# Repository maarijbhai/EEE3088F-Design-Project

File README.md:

# Micro Mouse Power Subsystem

This respository contains the datasheets of components used, schematics and production files of a power subsystem of a Micro Mouse. The power subsystem handles the charging, battery monitoring, motor controll and providing power to the various other subsections of a Micro Mouse.

## Table of Contents
- [Overview](#overview)
- [Subsytem Requirements](#subsystem-requirements)
- [File Structure](file-structure)
- [Usage](#usage)
- [Production](#production)
- [Credits](credits)

## Overview

Designed to navigate and solve a maze by itself, the Micro Mouse is a common project with even competitions made to determine who is able to create the fastest and most efficient Micro Mouse. While not on the competition level this project is undertaken by students in the University of Cape Town to put into practice all the theoretical knowledge learnt in their studies. With the hardware and sensoring subsystem designed by the university, the aim of this project is to design the power subsystem that powers the overall design.

## Subsystem Requirements

- Operate up to 4 motors bidirectionally with the pins available to you (listed in the power pinout table). You will need to control 2x brushed DC motors which could each draw 200mA at the highest voltage of a 1S1P battery (the battery is further specified in the battery section). The other 2x motors are for the auxiliary connection and need to operate 500mA each.
- Place an INA219 for monitoring the battery on the I2C Bus and configure it correctly with respect to the hardware (cannot have BOTH A0 AND A1 on GND)
- Charge the battery from the 9V input pin (listed in the power pinout table).
- Have two charging modes for a higher and lower charging current for the battery (200mA, and approximately 600mA ±100mA from the battery perspective.
- Integrate USB C and get 9V out of the USB Host
- Provide 2x External Load Switching at 1A each (High Side connected to your 5V)
- Provide a 3V3 5% accuracy (300mA max) and 5V Out 5% accuracy (1.5A max)
- Provide an ON/OFF switch. OFF state: battery draw <30uA. ON state: can provide your robot peak current of 2A. The switch needs to shut down 5V and 3V3.

## File Structure

Each of the above mentioned requirements are designed seperately under their own folder name ultimately meeting up in the Main project folder. This was to prevent any clashes or errors arising from outdated revisions of the project being worked on. 

The production files (gerbers) can be found inside the Main project folder under "JLCPCB".

## Usage

# Access schematic or PCB:
To view or modify the schematic and/or PCB:
1. Open KiCad 9 or later
2. Load the Main project (or any other desired)
3. Edit or simulate as needed

# To manufacture the PCB:
1. Navigate to the JLCPCB website
2. Upload the Gerber ZIP file
3. Use the provided BOM and CPL files in the JLCPCB file directory inside the main project folder for assembly

## Credits
- Maarij Alam
- Saeed Solomon

Third-party components from Texas Instruments, ON Semiconductor, and others.

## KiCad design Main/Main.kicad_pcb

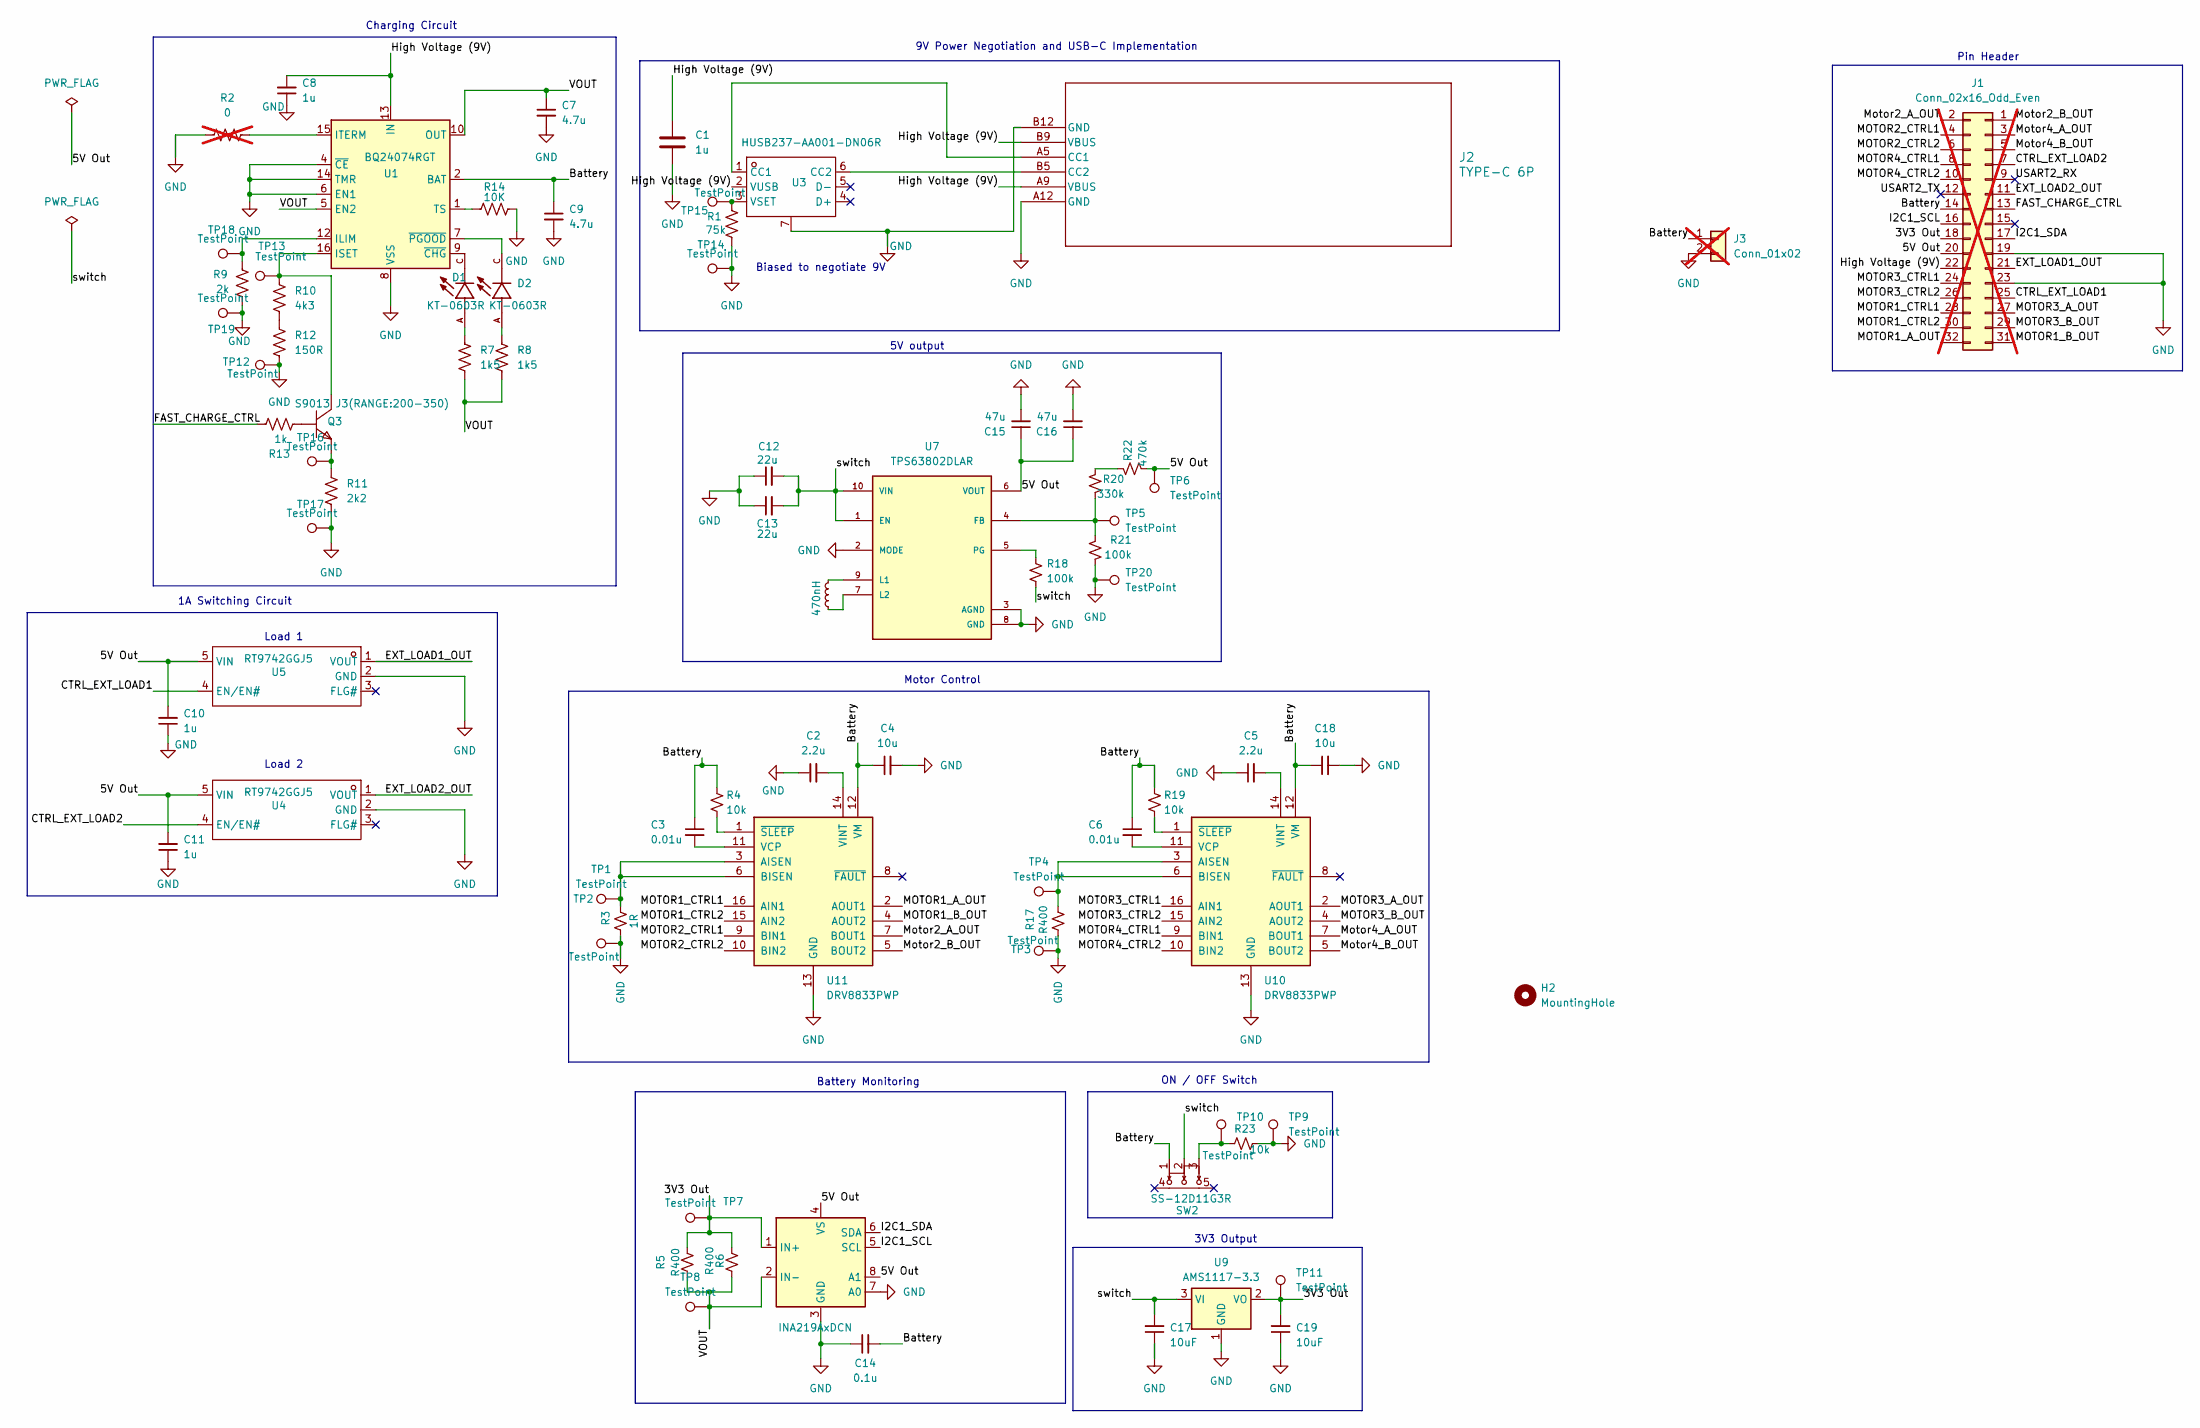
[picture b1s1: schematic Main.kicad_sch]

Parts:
C1, C8, C10, C11: 1u; C_1206_3216Metric_Pad1.33x1.80mm_HandSolder; LCSC C1848
C2, C5: 2.2u; C_0402_1005Metric_Pad0.74x0.62mm_HandSolder; LCSC C12530
C3, C6: 0.01u; C_0805_2012Metric_Pad1.18x1.45mm_HandSolder; LCSC C1710
C4, C18: 10u; C_0402_1005Metric_Pad0.74x0.62mm_HandSolder; LCSC C15525
C7: 4.7u; C_0402_1005Metric; LCSC C23733
C9: 4.7u; C_0402_1005Metric_Pad0.74x0.62mm_HandSolder; LCSC C23733
C12, C13: 22u; C_0402_1005Metric_Pad0.74x0.62mm_HandSolder; LCSC C45783
C14: 0.1u; C_0603_1608Metric_Pad1.08x0.95mm_HandSolder; LCSC C14663
C15, C16: 47u; C_0402_1005Metric_Pad0.74x0.62mm_HandSolder; LCSC C96123
C17, C19: 10uF; C_0402_1005Metric_Pad0.74x0.62mm_HandSolder; LCSC C19702
D1, D2: KT-0603R; LED_KT-0603R; PARTREV 2013/01/24
H2: MountingHole; MountingHole_3.2mm_M3
J1: Conn_02x16_Odd_Even; PinHeader_2x16_P2.54mm_Vertical; not fitted
J2: TYPE-C 6P; USB_C_Receptacle_GCT_USB4125-xx-x_6P_TopMnt_Horizontal; LCSC C668623
J3: Conn_01x02; JST_PH_S2B-PH-K_1x02_P2.00mm_Horizontal; not fitted
L1: 470nH; L_0603_1608Metric_Pad1.05x0.95mm_HandSolder
Q3: S9013 J3(RANGE:200-350); SOT-23_Handsoldering; MANUFACTURER PART S9013 J3(RANGE:200-350); LCSC PART NAME NPN 电流:500mA 耐压:25V H档(200-350)
R1: 75k; R_0603_1608Metric_Pad0.98x0.95mm_HandSolder; LCSC C23242
R2: 0; R_0402_1005Metric_Pad0.72x0.64mm_HandSolder; not fitted
R3: 1R; R_1206_3216Metric_Pad1.30x1.75mm_HandSolder; LCSC C17928
R4, R19: 10k; R_0402_1005Metric_Pad0.72x0.64mm_HandSolder; LCSC C17414
R5, R6, R17: R400; R_1206_3216Metric_Pad1.30x1.75mm_HandSolder; LCSC C247521
R7, R8: 1k5; R_0402_1005Metric_Pad0.72x0.64mm_HandSolder; LCSC C25867
R9: 2k; R_0402_1005Metric_Pad0.72x0.64mm_HandSolder; LCSC C4109
R10: 4k3; R_0402_1005Metric_Pad0.72x0.64mm_HandSolder; LCSC C25899
R11: 2k2; R_0402_1005Metric_Pad0.72x0.64mm_HandSolder; LCSC C25879
R12: 150R; R_0815_2038Metric_Pad1.20x4.05mm_HandSolder; LCSC C17471
R13: 1k; R_0402_1005Metric_Pad0.72x0.64mm_HandSolder
R14: 10K; R_0402_1005Metric_Pad0.72x0.64mm_HandSolder; LCSC C25744
R18, R21: 100k; R_0402_1005Metric_Pad0.72x0.64mm_HandSolder; LCSC C25741
R20: 330k; R_0603_1608Metric_Pad0.98x0.95mm_HandSolder; LCSC C23137
R22: 470k; R_0603_1608Metric_Pad0.98x0.95mm_HandSolder; LCSC C23178
R23: 10k; R_0402_1005Metric_Pad0.72x0.64mm_HandSolder; LCSC C25744
SW2: SS-12D11G3R; SW-TH_SS-12D11L3; CURRENT RATING (DC) 3A; VOLTAGE RATING (DC) 125V; MANUFACTURER PART SS-12D11G3R; LCSC PART NAME 柄长3mm 弯插双档 滑动开关
TP1, TP2, TP3, TP4, TP5, TP6, TP7, TP8, TP9, TP10, TP11, TP12, TP13, TP14, TP15, TP16, TP17, TP18, TP19, TP20: TestPoint; TestPoint_Pad_D1.0mm
U1: BQ24074RGT; VQFN-16-1EP_3x3mm_P0.5mm_EP1.6x1.6mm; LCSC C54313
U3: HUSB237-AA001-DN06R; DFN-6-1EP_2x2mm_P0.65mm_EP1.01x1.7mm; MANUFACTURER PART HUSB237-AA001-DN06R; LCSC PART NAME HUSB237-AA001-DN06R
U4, U5: RT9742GGJ5; TSOT-23-5_HandSoldering; INPUT VOLTAGE 2.7V~6V; MANUFACTURER PART RT9742GGJ5; LCSC PART NAME RT9742GGJ5
U6: INA219AxDCN; SOT-23-8_Handsoldering; LCSC C87469
U7: TPS63802DLAR; VREG_TPS63802DLAR; PARTREV B; DigiKey_Part_Number 296-TPS63802DLARTR-ND
U9: AMS1117-3.3; SOT-223-3_TabPin2; LCSC C6186
U10, U11: DRV8833PWP; HTSSOP-16-1EP_4.4x5mm_P0.65mm_EP3.4x5mm_Mask2.46x2.31mm; LCSC C1556089

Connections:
/3V3 Out: C19.2, J1.18, R5.2, R6.2, TP7.1, TP11.1, U6.1 (IN+), U9.2 (VO)
/5V Out: C10.2, C11.2, C15.1, C16.1, J1.20, R22.2, TP6.1, U4.5 (VIN), U5.5 (VIN), U6.4 (VS), U6.8 (A1), U7.6 (VOUT)
/Battery: C3.1, C4.1, C6.1, C9.1, C14.2, C18.1, J1.14, J3.1, R4.1, R19.1, SW2.1, U1.2 (BAT), U1.3 (BAT), U10.12 (VM), U11.12 (VM)
/CTRL_EXT_LOAD1: J1.25, U5.4 (EN/EN#)
/CTRL_EXT_LOAD2: J1.7, U4.4 (EN/EN#)
/EXT_LOAD1_OUT: J1.21, U5.1 (VOUT)
/EXT_LOAD2_OUT: J1.11, U4.1 (VOUT)
/FAST_CHARGE_CTRL: J1.13, R13.1
/High Voltage (9V): C1.1, C8.2, J1.22, J2.A9 (VBUS), J2.B9 (VBUS), U1.13 (IN), U3.2 (VUSB)
/I2C1_SCL: J1.16, U6.5 (SCL)
/I2C1_SDA: J1.17, U6.6 (SDA)
/MOTOR1_A_OUT: J1.32, U11.2 (AOUT1)
/MOTOR1_B_OUT: J1.31, U11.4 (AOUT2)
/MOTOR1_CTRL1: J1.28, U11.16 (AIN1)
/MOTOR1_CTRL2: J1.30, U11.15 (AIN2)
/MOTOR2_CTRL1: J1.4, U11.9 (BIN1)
/MOTOR2_CTRL2: J1.6, U11.10 (BIN2)
/MOTOR3_A_OUT: J1.27, U10.2 (AOUT1)
/MOTOR3_B_OUT: J1.29, U10.4 (AOUT2)
/MOTOR3_CTRL1: J1.24, U10.16 (AIN1)
/MOTOR3_CTRL2: J1.26, U10.15 (AIN2)
/MOTOR4_CTRL1: J1.8, U10.9 (BIN1)
/MOTOR4_CTRL2: J1.10, U10.10 (BIN2)
/Motor2_A_OUT: J1.2, U11.7 (BOUT1)
/Motor2_B_OUT: J1.1, U11.5 (BOUT2)
/Motor4_A_OUT: J1.3, U10.7 (BOUT1)
/Motor4_B_OUT: J1.5, U10.5 (BOUT2)
/USART2_RX: J1.9
/USART2_TX: J1.12
/VOUT: C7.1, R5.1, R6.1, R7.2, R8.2, TP8.1, U1.5 (EN2), U1.10 (OUT), U1.11 (OUT), U6.2 (IN-)
/switch: C12.2, C13.2, C17.2, R18.2, SW2.2, U7.1 (EN), U7.10 (VIN), U9.3 (VI)
GND: C1.2, C2.1, C4.2, C5.1, C7.2, C8.1, C9.2, C10.1, C11.1, C12.1, C13.1, C14.1, C15.2, C16.2, C17.1, C18.2, C19.1, J1.19, J1.23, J2.A12 (GND), J2.B12 (GND), J3.2, R1.2, R2.1, R3.1, R9.2, R11.2, R12.2, R14.2, R17.1, R21.2, R23.1, TP2.1, TP3.1, TP9.1, TP12.1, TP14.1, TP17.1, TP19.1, TP20.1, U1.4 (~CE), U1.6 (EN1), U1.8 (VSS), U1.14 (TMR), U1.17 (VSS), U3.7 (GND), U4.2 (GND), U5.2 (GND), U6.3 (GND), U6.7 (A0), U7.2 (MODE), U7.3 (AGND), U7.8 (GND), U9.1 (GND), U10.13 (GND), U10.17 (GND), U11.13 (GND), U11.17 (GND)
unnamed: D1.A, R7.1
unnamed: D2.A, R8.1
unnamed: J2.A5 (CC1), U3.1 (CC1)
unnamed: J2.B5 (CC2), U3.6 (CC2)
unnamed: Q3.1 (B), R13.2
unnamed: Q3.3 (C), R10.1, TP13.1, U1.16 (ISET)
unnamed: Q3.2 (E), R11.1, TP16.1
unnamed: R10.2, R12.1
unnamed: R20.1, R22.1
unnamed: R23.2, SW2.3, TP10.1
unnamed: R9.1, TP18.1, U1.12 (ILIM)
unnamed: R2.2, U1.15 (ITERM)
unnamed: R14.1, U1.1 (TS)
unnamed: D1.C, U1.9 (~CHG)
unnamed: D2.C, U1.7 (~PGOOD)
unnamed: R1.1, TP15.1, U3.3 (VSET)
unnamed: R20.2, R21.1, TP5.1, U7.4 (FB)
unnamed: L1.2, U7.9 (L1)
unnamed: L1.1, U7.7 (L2)
unnamed: R18.1, U7.5 (PG)
unnamed: R17.2, TP4.1, U10.3 (AISEN), U10.6 (BISEN)
unnamed: C6.2, U10.11 (VCP)
unnamed: C5.2, U10.14 (VINT)
unnamed: R19.2, U10.1 (~SLEEP)
unnamed: R3.2, TP1.1, U11.3 (AISEN), U11.6 (BISEN)
unnamed: C3.2, U11.11 (VCP)
unnamed: C2.2, U11.14 (VINT)
unnamed: R4.2, U11.1 (~SLEEP)

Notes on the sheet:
ON / OFF Switch
1A Switching Circuit
Battery Monitoring
Pin Header
9V Power Negotiation and USB-C Implementation
Charging Circuit
5V output
3V3 Output
Motor Control
Biased to negotiate 9V
Load 2
Load 1

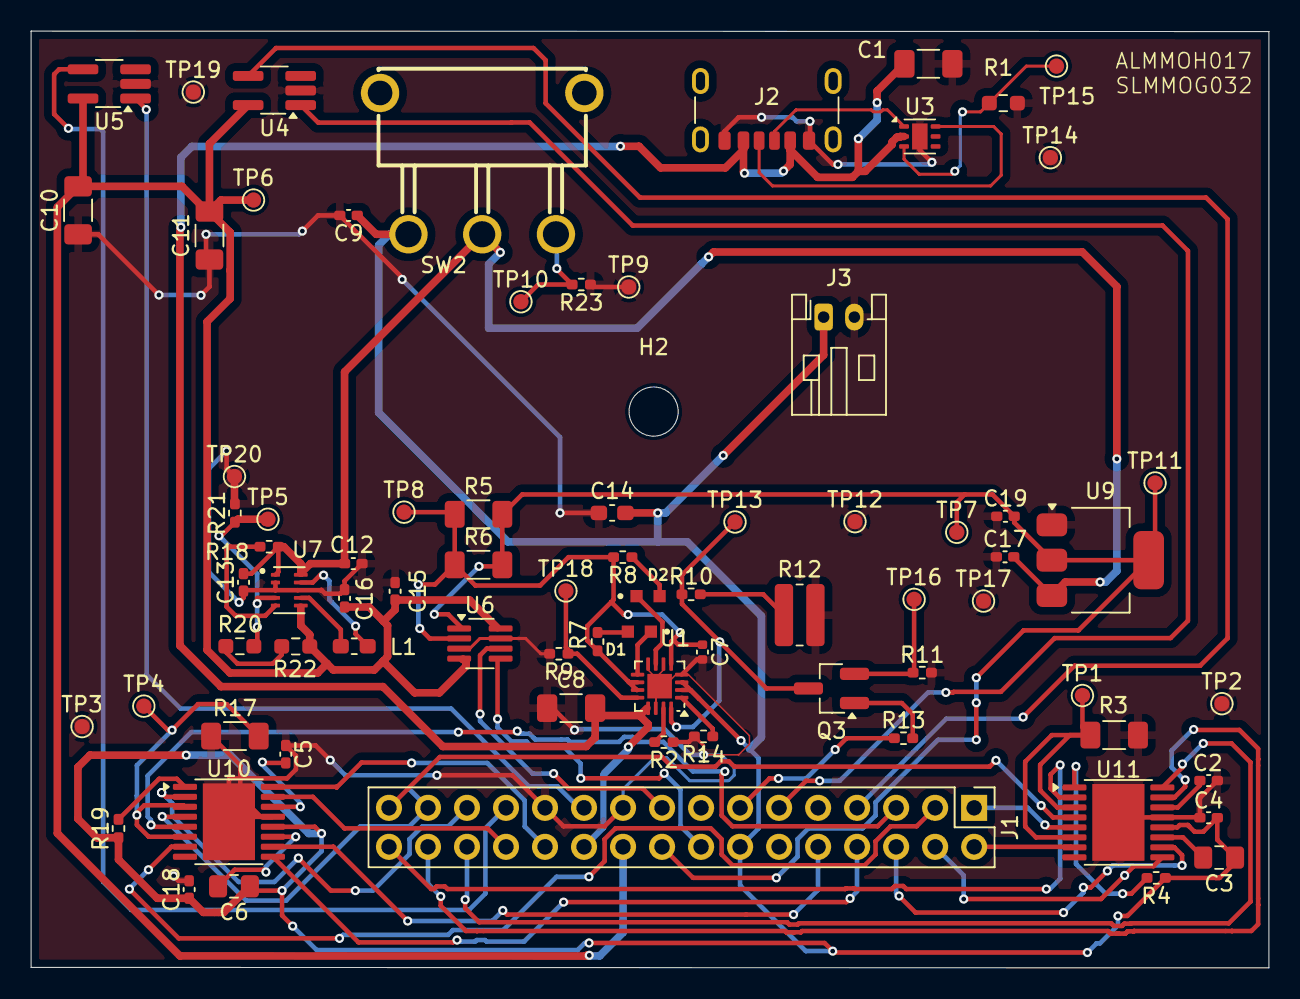
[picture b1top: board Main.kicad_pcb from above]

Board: 2 copper layers, 80.6 x 61.0 mm, 78 parts (0 on the bottom side), 58 nets.

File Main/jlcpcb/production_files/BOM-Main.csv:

Comment,Designator,Footprint,LCSC,Quantity
2.2u,"C2,C5",C_0402_1005Metric_Pad0.74x0.62mm_HandSolder,C12530,2
0.1u,C14,C_0603_1608Metric_Pad1.08x0.95mm_HandSolder,C14663,1
10u,"C18,C4",C_0402_1005Metric_Pad0.74x0.62mm_HandSolder,C15525,2
0.01u,"C3,C6",C_0805_2012Metric_Pad1.18x1.45mm_HandSolder,C1710,2
10k,"R19,R4",R_0402_1005Metric_Pad0.72x0.64mm_HandSolder,C17414,2
150R,R12,R_0815_2038Metric_Pad1.20x4.05mm_HandSolder,C17471,1
1R,R3,R_1206_3216Metric_Pad1.30x1.75mm_HandSolder,C17928,1
1u,"C1,C10,C11,C8",C_1206_3216Metric_Pad1.33x1.80mm_HandSolder,C1848,4
10uF,"C17,C19",C_0402_1005Metric_Pad0.74x0.62mm_HandSolder,C19702,2
HUSB237-AA001-DN06R,U3,DFN-6-1EP_2x2mm_P0.65mm_EP1.01x1.7mm,C22373734,1
330k,R20,R_0603_1608Metric_Pad0.98x0.95mm_HandSolder,C23137,1
470k,R22,R_0603_1608Metric_Pad0.98x0.95mm_HandSolder,C23178,1
75k,R1,R_0603_1608Metric_Pad0.98x0.95mm_HandSolder,C23242,1
4.7u,"C7,C9",C_0402_1005Metric,C23733,2
R400,"R17,R5,R6",R_1206_3216Metric_Pad1.30x1.75mm_HandSolder,C247521,3
RT9742GGJ5,"U4,U5",TSOT-23-5_HandSoldering,C250547,2
100k,"R18,R21",R_0402_1005Metric_Pad0.72x0.64mm_HandSolder,C25741,2
10K,"R14,R23",R_0402_1005Metric_Pad0.72x0.64mm_HandSolder,C25744,2
1k5,"R7,R8",R_0402_1005Metric_Pad0.72x0.64mm_HandSolder,C25867,2
2k2,R11,R_0402_1005Metric_Pad0.72x0.64mm_HandSolder,C25879,1
4k3,R10,R_0402_1005Metric_Pad0.72x0.64mm_HandSolder,C25899,1
TPS63802DLAR,U7,VREG_TPS63802DLAR,C2845237,1
2k,R9,R_0402_1005Metric_Pad0.72x0.64mm_HandSolder,C4109,1
22u,"C12,C13",C_0402_1005Metric_Pad0.74x0.62mm_HandSolder,C45783,2
BQ24074RGT,U1,VQFN-16-1EP_3x3mm_P0.5mm_EP1.6x1.6mm,C54313,1
AMS1117-3.3,U9,SOT-223-3_TabPin2,C6186,1
TYPE-C 6P,J2,USB_C_Receptacle_GCT_USB4125-xx-x_6P_TopMnt_Horizontal,C668623,1
S9013 J3(RANGE:200-350),Q3,SOT-23_Handsoldering,C6749,1
INA219AxDCN,U6,SOT-23-8_Handsoldering,C87469,1
47u,"C15,C16",C_0402_1005Metric_Pad0.74x0.62mm_HandSolder,C96123,2
DRV8833PW,U2,TSSOP-16_4.4x5mm_P0.65mm,,1
TestPoint,TP18,TestPoint_Pad_D1.0mm,,1
TestPoint,TP11,TestPoint_Pad_D1.0mm,,1
TestPoint,TP4,TestPoint_Pad_D1.0mm,,1
DRV8833PW,U8,TSSOP-16_4.4x5mm_P0.65mm,,1
1k,R13,R_0402_1005Metric_Pad0.72x0.64mm_HandSolder,,1
TestPoint,TP14,TestPoint_Pad_D1.0mm,,1
TestPoint,TP13,TestPoint_Pad_D1.0mm,,1
TestPoint,TP2,TestPoint_Pad_D1.0mm,,1
KT-0603R,D1,LED_KT-0603R,,1
TestPoint,TP6,TestPoint_Pad_D1.0mm,,1
TestPoint,TP15,TestPoint_Pad_D1.0mm,,1
TestPoint,TP9,TestPoint_Pad_D1.0mm,,1
TestPoint,TP12,TestPoint_Pad_D1.0mm,,1
TestPoint,TP16,TestPoint_Pad_D1.0mm,,1
TestPoint,TP8,TestPoint_Pad_D1.0mm,,1
KT-0603R,D2,LED_KT-0603R,,1
TestPoint,TP17,TestPoint_Pad_D1.0mm,,1
TestPoint,TP3,TestPoint_Pad_D1.0mm,,1
TestPoint,TP19,TestPoint_Pad_D1.0mm,,1
TestPoint,TP5,TestPoint_Pad_D1.0mm,,1
TestPoint,TP10,TestPoint_Pad_D1.0mm,,1
SS-12D11G3R,SW2,SW-TH_SS-12D11L3,,1
TestPoint,TP1,TestPoint_Pad_D1.0mm,,1
470nH,L1,L_0603_1608Metric_Pad1.05x0.95mm_HandSolder,,1
TestPoint,TP7,TestPoint_Pad_D1.0mm,,1
TestPoint,TP20,TestPoint_Pad_D1.0mm,,1

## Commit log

2025-03-19 Create hello unc.txt
    test
2025-03-19 replied
2025-03-19 hello unc.txt
2025-03-20 Added all the job splits
2025-03-21 INA219 configuration
    Added a KiCad project to set up and configure the INA219. Datasheet attached as well.
2025-03-23 Started 3V3 and 5V out
    Started working in the 3V3 and 5V output module and assigned footprints to the INA219 module
2025-03-24 USB C Data Sheets and Misc
2025-03-24 USB C Integration KiCad
2025-03-24 Update hello unc.txt
    fixed the split
2025-03-24 Added bidirectional motor control section
    Completed the bidirectional motor control part of the system as well as finished the remaining part of the 3V3 and 5V out.
2025-03-25 All MJ's requirements schematics done (review pending)
2025-03-26 ON/OFF switch
    Completed the ON/OFF switch.
2025-03-26 Changed switch
    Changed switch do not depend on p-mosfet
2025-03-26 Polished USB C Power and Charging Integration and Switching Circuit with Footprints
2025-03-26 Made it look more professional
2025-03-26 Created the Main File combining our schematics
2025-03-26 Some few fixes on pin assignments
2025-03-27 Added footprints
    Added footprints for a few missing ICs
2025-03-27 Changed pins
2025-03-27 added other footprints
2025-03-27 Changed Some Pin Names
2025-03-27 Made some pin label changes
2025-03-27 push before pcb
2025-03-27 Started PCB and Started Adding test points
2025-03-27 Got ALL the footprints present
2025-03-27 connected first motor control
2025-03-27 Did some error fixing
2025-03-27 Corrected LCSC of parts
    Initially accidentally labelled the LCSC of components as (LSCS) which generated an error. This version fixed these issues.
2025-03-27 Changed maximum motor voltage
2025-03-28 Completed substantial PCB Connections
    Completed: 1A Switching, Charging IC
2025-03-28 Finished 9V implementation and PD system
2025-03-28 Added the Switch and Connected the Battery pin to it
2025-03-28 Removed the GND for one of the motor ICs
    Pouring ground so ground not connected
2025-03-28 PB-13 was unconnected - it is now connected
2025-03-28 Changed all my 9V wires to 0,5mm
2025-03-28 connected other motor
2025-03-28 Poured Ground and connected all PCB items
2025-03-28 Using a new Motor Driver bc old one no stock
2025-03-28 NO ERRORS
2025-04-13 Changed Folders
    Neatened up the repository by renaming folders and deleting any unnecessary items.
